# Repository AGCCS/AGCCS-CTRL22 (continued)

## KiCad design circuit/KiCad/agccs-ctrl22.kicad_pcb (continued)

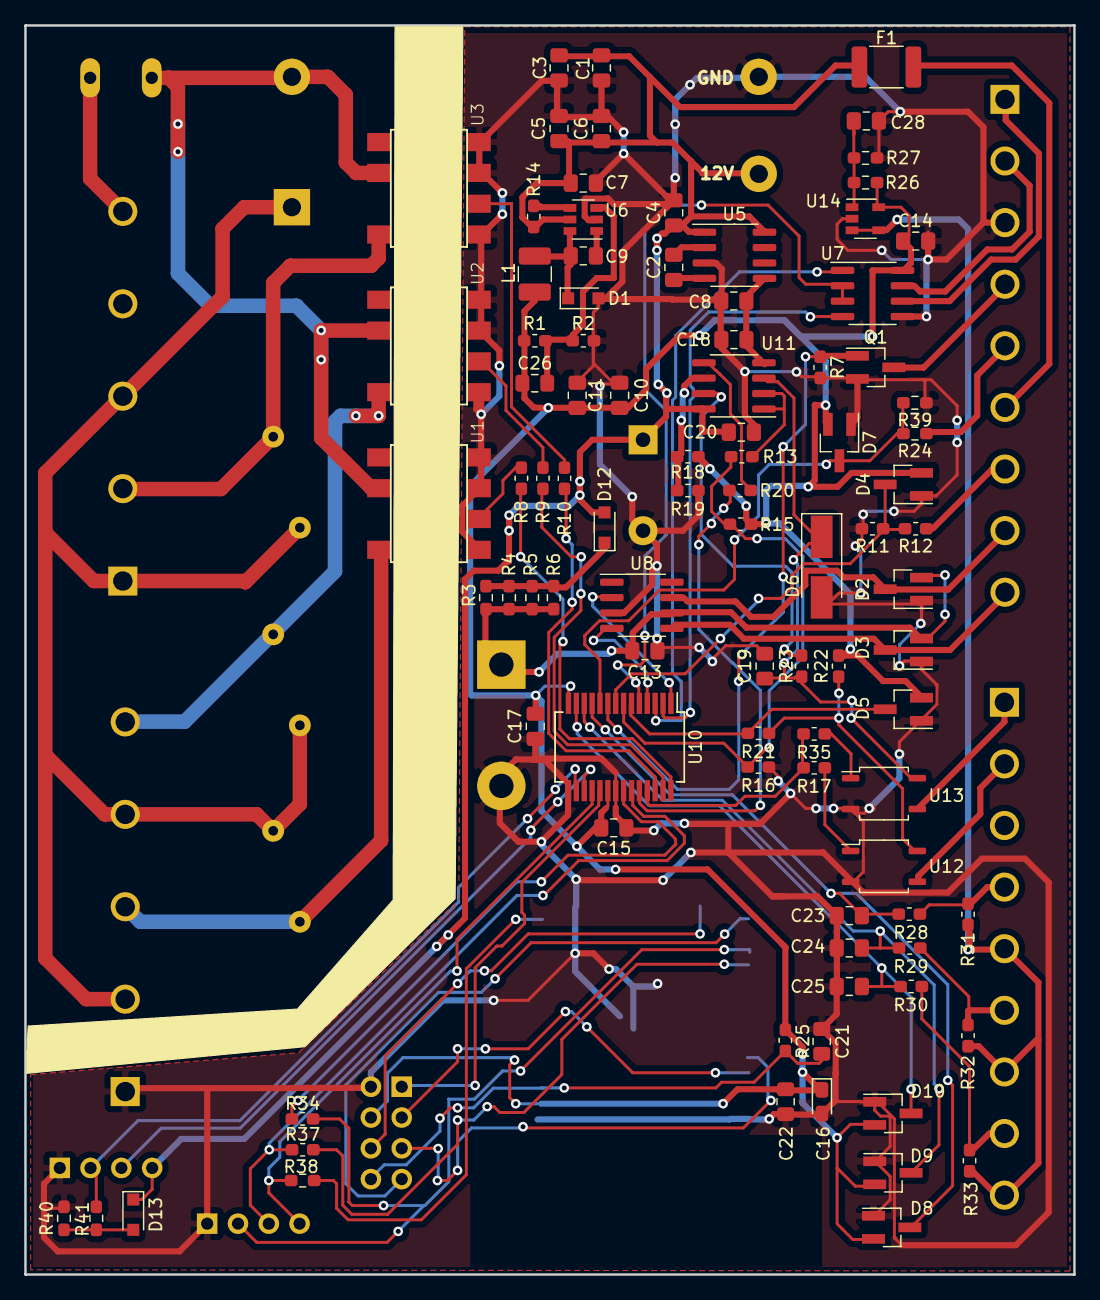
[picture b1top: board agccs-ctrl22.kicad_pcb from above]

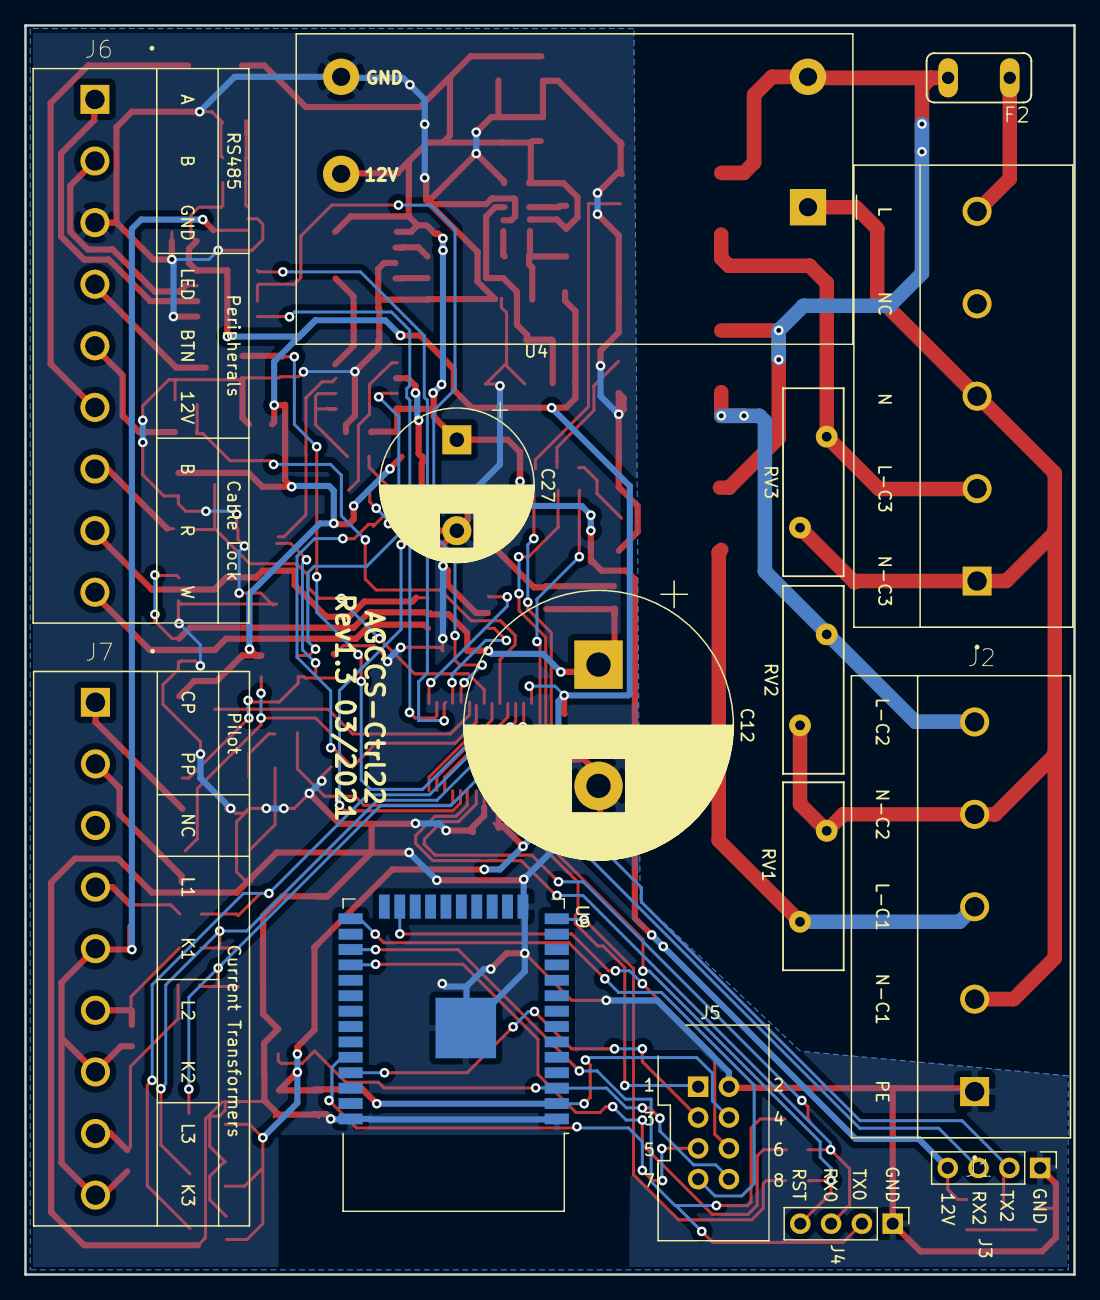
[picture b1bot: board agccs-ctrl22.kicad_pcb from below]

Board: 2 copper layers, 86.5 x 103.0 mm, 108 parts (15 on the bottom side), 77 nets.

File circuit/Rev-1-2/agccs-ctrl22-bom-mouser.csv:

;Reference;Value;Mouser PartNo;
;C1-C3, C5, C6, C8, C10, C11;10u16V;963-EMK212ABJ106MG-T;8
;C4, C7, C9, C13-C15, C17, C18, C20, C23-C25, C28;100n;963-EMF212B7104KGHT;13
;C12;15000u16V;871-B41231A4159M000;1
;C16;100u6.3V;581-TLCR107M006RTA;1
;C19;270p;77-VJ0805A271KXJPBC;1
;C21;1n50V;77-VJ0805A102KXAAC;1
;C22;1u10V;77-VJ805Y105KXARW1BC;1
;C26;100p;77-VJ0805Y101KXACBC;1
;C27;2200u16V;871-B41888C4228M000;1
;D1, D12;PMEG4010BEA;771-PMEG4010BEA,135;2
;D2-D5, D7-D10;BAT54S;757-TBAT54SLM;8
;D6;SMAJ13CA;652-SMAJ13CA;1
;D13;9.1;621-UDZ9V1BQ-13;1
;F1;FSMD020;576-1812L020PR;1
;F2;T1.25A;576-3921125000;1
;J1;Screw_Terminal_01x05;na;1
;J2;Screw_Terminal_01x05;490-TB005-762-10BE;1
;J3;Conn_01x04;710-61304011121;1
;J4;Conn_01x04;na;1
;J5;Conn_02x04;710-61200821621;1
;J6;Screw_Terminal_01x09;na;1
;J7;Screw_Terminal_01x09;490-TB004-508-18BE;1
;L1;3.3u;810-MLF1608A3R3J;1
;Q1;BSS138;512-BSS138;1
;R1;31.6k;594-MCT06030C3162FP5;1
;R2, R7, R15, R21, R26, R27;10k;594-MCT06030C1002FP5;6
;R3-R6, R8-R10, R28-R30;100;490-TB005-762-10BE;10
;R12, R24;5.6k;594-MCT06030C5601FP5;2
;R13;62k;594-MCT06030C6202FP5;1
;R14;100k;594-MCT06030C1003FP5;1
;R16, R18-R20;15k;594-MCT06030C1502FP5;4
;R22, R23;1k 1%;594-MCT06030C1001FP5;2
;R25;12k;594-MCT06030C1202FP5;1
;R31-R33;22;594-MCT06030C2209FP5;3
;R11, R17, R35, R39, R40;2k;594-MCT06030C2001FP5;5
;R34, R37, R38, R41;1k;594-MCT06030C1001FP5;4
;RV1-RV3;Varistor;871-B72214S0271K551;3
;U1-U3;AQH3223;769-AQH1213AX;3
;U4;IRM-10-12;709-IRM10-12;1
;U5;TC7660SEOA;579-TC7660SEOA;1
;U6;AP5100;621-AP5100WG-7;1
;U7;SN65HVD72C;595-SN65HVD72D;1
;U8;FAN3214TMX;512-FAN3214TMX;1
;U9;ESP32-WROOM-32;356-ESP32WRM32E128PH;1
;U10;ATmega4808-X;556-ATMEGA4808-XF;1
;U11;LM7332;926-LM7332MA/NOPB;1
;U12, U13;CPC1114N;849-CPC1114N;2
;U14;LM321LV;595-LM321LVIDBVR;1

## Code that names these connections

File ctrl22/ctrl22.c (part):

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*************************************************************************
*/

// the led is either on PD3 or PF0, depending on the board
#define LED_PD3
//define LED_PF0

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// baudrate formula from Atmel documentation
#define USART_BAUD_RATE(BAUD_RATE) (uint16_t) ( (F_CPU * 64.0) / (16.0 * BAUD_RATE) + 0.5 ) 

// component: init serial line on usart0 qith pins PA0 (TX) and PA1 (RX)
void serial_init(void) {
  USART0.BAUD  = USART_BAUD_RATE(115200);                                // set baud rate
  USART0.CTRLC = USART_CHSIZE_8BIT_gc | USART_PMODE_DISABLED_gc;         // 8 data bits, one stop bit, no parity
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
void dio_init(){
  // SSRs
  PORTA.DIRSET = (PIN6_bm | PIN5_bm | PIN4_bm);   // SSR1, SSR2 and SSR3 on PA6, PA5 and PA4
  PORTA.OUTCLR = (PIN6_bm | PIN5_bm | PIN4_bm);   // all SSRs default to off
  // signal relay
  PORTA.DIRSET = PIN3_bm;                         // signal relay on PA3
  PORTA.OUTSET = PIN3_bm;                         // inverted driver SET<>off
  // lock drive
  PORTA.DIRSET = PIN7_bm;                         // lock drive A on PA7 (red wire)
  PORTA.OUTSET = PIN7_bm;                         // defaults to on
  PORTC.DIRSET = PIN2_bm;                         // lock drive B on PC2 (white wire)
  PORTC.OUTSET = PIN2_bm;                         // defaults to on
  // lock state
  PORTD.DIRCLR = PIN2_bm;                         // lock state on PD2 (black wire)
  // brown out
  PORTF.DIRCLR = PIN0_bm;                         // brown out signal is of PF0)
}


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  // no brown-out detection in early boards
  if(p_boardrev<1.2) return;
  // read brown-out detector
  bool bot = !(PORTF.IN & PIN0_bm);
  if(!bot) return;
  ldrive(ldopen);
  ssr(0);
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*************************************************************************
synchronous analog reading with ADC0
- internal temperature sensor 
- contact pilot CP on PD1
- proximity pilot PP pn PD0
- periodic update by main loop callback
*************************************************************************
*/
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  ADC0.INTCTRL = 0x00;                   // no interrupts
  ADC0.CTRLA |= ADC_ENABLE_bm;
  // run conversion contact pilot CP
  ADC0.MUXPOS = ADC_MUXPOS_AIN1_gc;      // select CP on PD1
  while(TCA0.SINGLE.CNT < 250);          // wait for dualslope PWM to be low
  while(TCA0.SINGLE.CNT > 250);          // wait for dualslope PWM to just become be high for level reading
  ADC0.COMMAND = ADC_STCONV_bm;
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    g_cpnslp=dtv;
  }
  // run conversion proximity pilot PP
  ADC0.MUXPOS = ADC_MUXPOS_AIN0_gc;      // select PP on PD0
  ADC0.COMMAND = ADC_STCONV_bm;
  while (!(ADC0.INTFLAGS & ADC_RESRDY_bm));
  int16_t pp=ADC0.RES;
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*************************************************************************
*/

// prepare current tranformer pins PD5,PD6 and PD7 for adc input
void rms_init(void) {
  PORTD.DIRCLR = PIN5_bm;
  PORTD.PIN5CTRL &= ~PORT_ISC_gm;
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  
/*
*************************************************************************
PWM output for CP driven by TCA on PA2
- 1kHz dual slope PWM
*************************************************************************
*/
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  TCA0.SINGLE.CTRLA |= TCA_SINGLE_CLKSEL_DIV1_gc;      // set clock to 10MHz, 100ns per tick
  TCA0.SINGLE.CTRLB |= TCA_SINGLE_WGMODE_DSBOTTOM_gc;  // set to dual slope mode
  TCA0.SINGLE.PER    = 5000;                           // 1ms = 2 * period * 100ns >> period= 5000;
  TCA0.SINGLE.CMP2   = 500;                            // use cmp2 for PWM of PA2, default duty cycle 10% for testing  
  TCA0.SINGLE.CTRLB &= ~TCA_SINGLE_CMP2EN_bm;          // disable output    
  TCA0.SINGLE.CTRLA |= TCA_SINGLE_ENABLE_bm;           // start timer (timer runs allways == relevant for CP reading)
}
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
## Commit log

2021-02-16 learning git
2021-02-16 first steps
2021-02-16 till going
2021-02-16 first
2021-02-16 lets go
